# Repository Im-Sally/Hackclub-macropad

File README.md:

# Hackclub-macropad

A small programmable macropad for 3D modelling with 9 buttons, an OLED screen and 2 status LEDs on an external PCB. The OLED is mounted in the lid, so replacing it later is easy I'll just need to desolder four wires and print a new lid. The display connects to the PCB using four wires soldered to the pads located in the top right corner of the board. The 2 LED's are mounted on an small PCB attached to the main PCB with a snap point so it can be separated and connected with wires and put in the lid. I haven't made any firmware for this becuase I can't debug it.

## Bill of Materials for this project)

- 1× 3D-printed case
- 1× Seeed XIAO RP2040
- 1x ssd1306 oled-0.91-128x32
- 1× PCB
- 2x SK6812 MINI-E LEDs
- 4x M3x16mm screws
- 4x M3x5mx4mm heatset inserts
- 9x Through-hole 1N4148 Diodes
- 9× MX-Style switches
- 9x Blank DSA keycaps (White)

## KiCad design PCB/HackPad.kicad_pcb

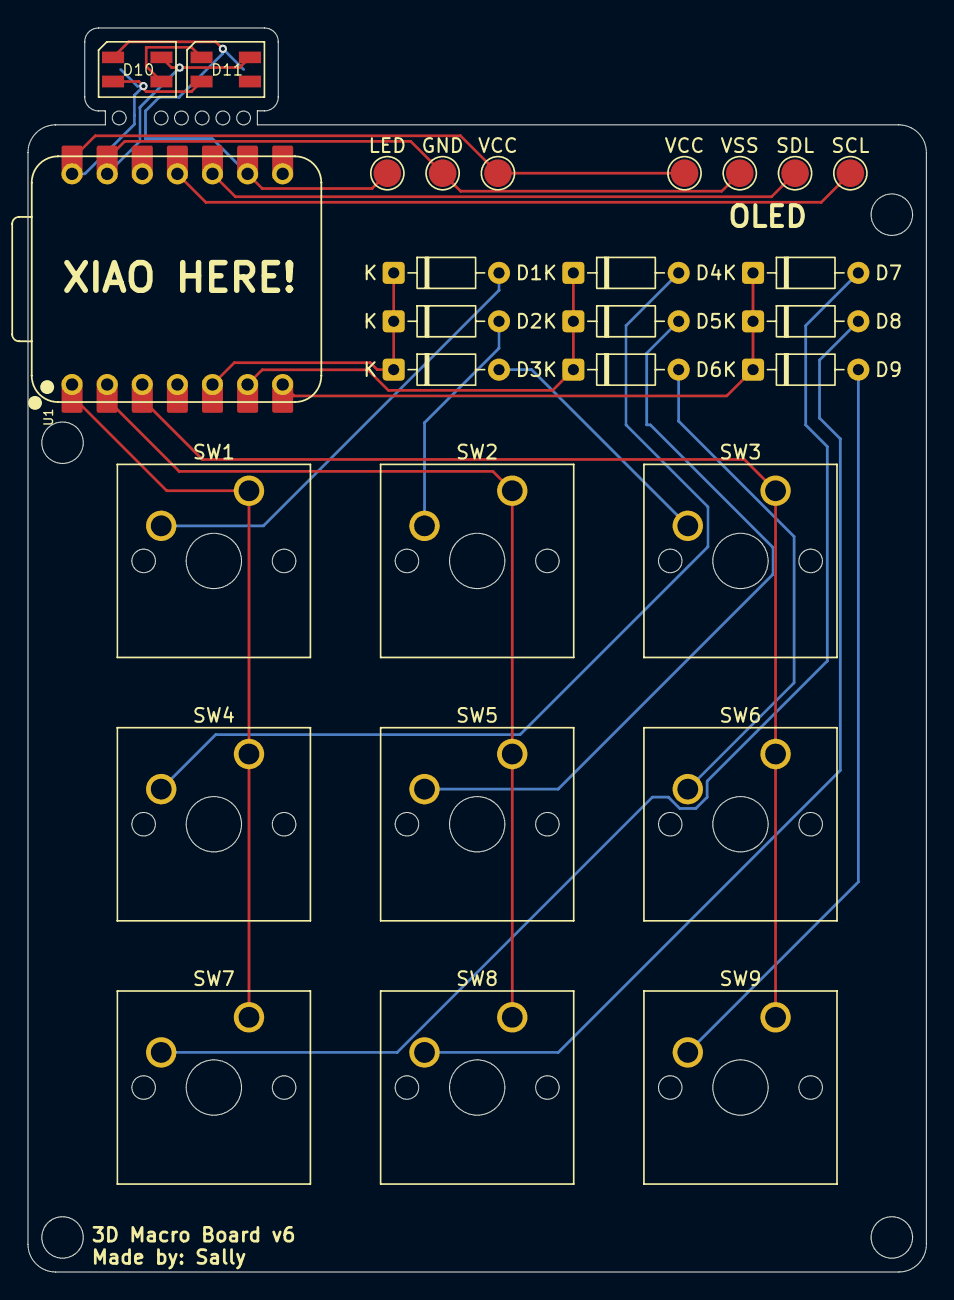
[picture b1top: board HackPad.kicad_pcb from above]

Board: 2 copper layers, 65.0 x 90.0 mm, 31 parts (0 on the bottom side), 21 nets.

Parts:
D1, D2, D3, D4, D5, D6, D7, D8, D9: 1N4148; D_DO-35_SOD27_P7.62mm_Horizontal
D10, D11: SK6812MINI; LED_SK6812MINI_PLCC4_3.5x3.5mm_P1.75mm
GND: TestPoint; TestPoint_Pad_D2.0mm
GND#2: TestPoint; TestPoint_Pad_D2.0mm
LED: TestPoint; TestPoint_Pad_D2.0mm
LED#2: LED; TestPoint_Pad_D2.0mm
SCL: TestPoint; TestPoint_Pad_D2.0mm
SDL: TestPoint; TestPoint_Pad_D2.0mm
SW1, SW2, SW3, SW4, SW5, SW6, SW7, SW8, SW9: SW_Push; SW_Cherry_MX_1.00u_PCB
U1: XIAO-RP2040-DIP
VCC: TestPoint; TestPoint_Pad_D2.0mm
VCC#2, VCC#3: TestPoint; TestPoint_Pad_D2.0mm
VSS: TestPoint; TestPoint_Pad_D2.0mm

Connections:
+5V: D10.4 (VDD), D11.4 (VDD), U1.14 (VBUS), VCC.1, VCC#2.1, VCC#3.1
/Col0: SW1.1, SW4.1, SW7.1, U1.1 (GPIO26/ADC0/A0)
/Col1: SW2.1, SW5.1, SW8.1, U1.2 (GPIO27/ADC1/A1)
/Col2: SW3.1, SW6.1, SW9.1, U1.3 (GPIO28/ADC2/A2)
/Row0: D1.1 (K), D2.1 (K), D3.1 (K), U1.5 (GPIO6/SDA)
/Row1: D4.1 (K), D5.1 (K), D6.1 (K), U1.6 (GPIO7/SCL)
/Row2: D7.1 (K), D8.1 (K), D9.1 (K), U1.7 (GPIO0/TX)
GND: D10.2 (VSS), D11.2 (VSS), GND.1, GND#2.1, U1.13 (GND), VSS.1
unnamed: D1.2 (A), SW1.2
unnamed: D2.2 (A), SW2.2
unnamed: D3.2 (A), SW3.2
unnamed: D4.2 (A), SW4.2
unnamed: D5.2 (A), SW5.2
unnamed: D6.2 (A), SW6.2
unnamed: D7.2 (A), SW7.2
unnamed: D8.2 (A), SW8.2
unnamed: D9.2 (A), SW9.2
unnamed: D10.3 (DIN), LED.1, LED#2.1, U1.9 (GPIO2/SCK)
unnamed: D10.1 (DOUT), D11.3 (DIN)
unnamed: SCL.1, U1.11 (GPIO3/MOSI)
unnamed: SDL.1, U1.10 (GPIO4/MISO)

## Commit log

2025-12-05 Add README
2025-12-05 Fix image paths for schematic and PCB
    Updated image references in README for schematic and PCB.
2025-12-05 Rename model1.png to model.png
2025-12-05 Rename pcb1.png to pcb.png
2025-12-05 Rename schematic1.png to schematic.png
2025-12-05 Enhance README with OLED screen information
    Updated the description to include an OLED screen.
2025-12-06 Enhance README with OLED screen details
    Expanded description of the macropad's OLED screen and its connection.
2025-12-06 Refine README.md description for clarity
    Improved readability and clarity of the description.
2025-12-06 Enhance README with new LEDs and images
    Updated the README to include additional components and images.
2025-12-06 Fix image paths in README.md
2025-12-07 Revise README for macropad details and images
    Updated the description of the macropad to clarify the components and their connections. Added a new image for the back of the PCB.
2025-12-07 Update README with firmware debugging note
    Added a note about firmware debugging.
2025-12-07 Remove OLED top view image from README
    Removed the OLED view from the top image from the README.
